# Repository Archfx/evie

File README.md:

# Camaro6 CAD files
### EVIE is my 6<sup>th</sup> gen Camaro

This repository contains various CAD models I have designed for 6th-generation Camaros built on the [alpha platform](https://en.wikipedia.org/wiki/General_Motors_Alpha_platform). 
These models were created using [FreeCAD](https://www.freecad.org/) and [KiCad](https://www.kicad.org/). 

Electric Vacuum Pump
---

The mount is designed for installing the GM electric vacuum pump from the C7 Corvette onto 6th-generation LTG Camaros. It attaches directly to the existing bolt holes in the passenger-side engine compartment, next to the downpipe. No additional drilling is required.

Fire Extinguisher Mount
---

This directly mounts to the rear rails of the passenger seat. 

Assembly Requires the Following Items:
- Fire extinguisher and the mounting bracket (I used a [First Alert](https://www.firstalert.com/))
- Mounting hardware for the bracket
- 2x 6mm steel standoff (24mm height)
- 2x 6mm hex nut and bolt
- Drill

Note: You may need to slightly enlarge the left rail bolt hole to accommodate a 6 mm standoff. Alternatively, a 5 mm standoff can be used without any modification.

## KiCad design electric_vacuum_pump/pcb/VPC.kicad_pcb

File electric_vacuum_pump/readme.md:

Relay Box Parts
----

- CID101-2.8-FS4 Original Yazaki 7116-4153-02 Terminal, YESC 2.8 mm, Female, 3.0 - 4.0 mm² × 2

- MTA 0301504 MiniVAL / Mini Relay Gray Module × 1

- CID101-2.8-MS4 Original Yazaki 7114-4153-02 Terminal , Male, 3.0 - 4.0 mm² × 4

- MTA 1708332-L Mini 280 Female Terminal, Unsealed, 2.5 - 4.0 mm² × 4

- MTA 1708500-L Female Terminal, 630 Series, Unsealed, 0.35 - 0.5 mm² × 8

- MTA 1708502-L Female Terminal, 630 Series, Unsealed, 2.0 - 3.0 mm² × 6

- MTA 0301506 Secondary Lock for 0301504 Gray Module × 1

- CID203-2.3-FS1 Drop In for Sumitomo 1500-0106 Sealed Female 090 Terminals, 0.3 -0.5 mm², Tin Plated × 5

- CID2026J-2.3-21 Drop In for Sumitomo 2-way Sealed Female MT090 Connector 6180-2327, Light Gray × 2

- CID203-2.3-MS2 Drop In for Sumitomo 1500-0105 Male Terminal 090, 0.85 - 1.25 mm², Tin Plating × 5

- CID2026J-2.3-11 Drop In for Sumitomo 2-way Sealed Male MT090 Connector 6187-2317, Light Gray × 2

- MAH-S-112-C-1D2 ISO Mini Relay 60A, 12Vdc, SPDT with Diode Suppression Drop in for Song Chuan 896H-1CH-C-002-12VDC × 1

- MTA 0301590 Cover for a Single Gray Module × 1

- MTA 0301580 Mounting Bracket for Gray Modules × 2

- MTA 0705160 MiniVAL 25 Amp Fuse, White × 3

- CID3110 Original Yazaki 7158-3110-40 Wire Seal, YESC 2.8 mm, Gray, Silicone × 4

- CID101-2.8-MS4 Original Yazaki 7114-4153-02 Terminal , Male, 3.0 - 4.0 mm² × 4

Controller PCB Parts
---

| Id | Designator | Footprint                           | Quantity | Designation     |
|----|------------|-------------------------------------|----------|-----------------|
| 1  | U3         | HPAK_16AH-E_STM                     | 1        | VN5T016AHTR-E   |
| 2  | LED1       | LED_0603_1608Metric                 | 1        | LED_0603        |
| 3  | U2         | Converter_DCDC_TRACO_TSR1-xxxxE_THT | 1        | TSR1-2450E      |
| 4  | R3         | R_0603_1608Metric                   | 1        | 1K_R_0603       |
| 5  | R5         | R_0603_1608Metric                   | 1        | 1k              |
| 6  | J1         | PinHeader_1x01_P2.54mm_Vertical     | 1        | Program         |
| 7  | J2         | PinHeader_1x05_P2.54mm_Vertical     | 1        | Mini Relay Pins |
| 8  | U1         | SOIC-8_3.9x4.9mm_P1.27mm            | 1        | ATtiny412-SS    |
| 9  | C4,C5      | C_0603_1608Metric                   | 2        | 10nf            |
| 10 | R2,R4,R7   | R_0603_1608Metric                   | 3        | 56K             |
| 11 | FB1        | C_0603_1608Metric                   | 1        | BLM18PG121SN1D  |
| 12 | C1         | C_1812_4532Metric                   | 1        | 22uf            |
| 13 | R6         | R_0603_1608Metric                   | 1        | 10R             |
| 14 | C6,C3      | C_0603_1608Metric                   | 2        | 100nf           |
| 15 | R8,R1      | R_0603_1608Metric                   | 2        | 100K            |
| 16 | D1         | D_SMB                               | 1        | SMBJ24A-Q       |
| 17 | D3         | D_SOD-323                           | 1        | PESD5V0S1BA     |
| 18 | C2         | C_1210_3225Metric                   | 1        | 10uf            |

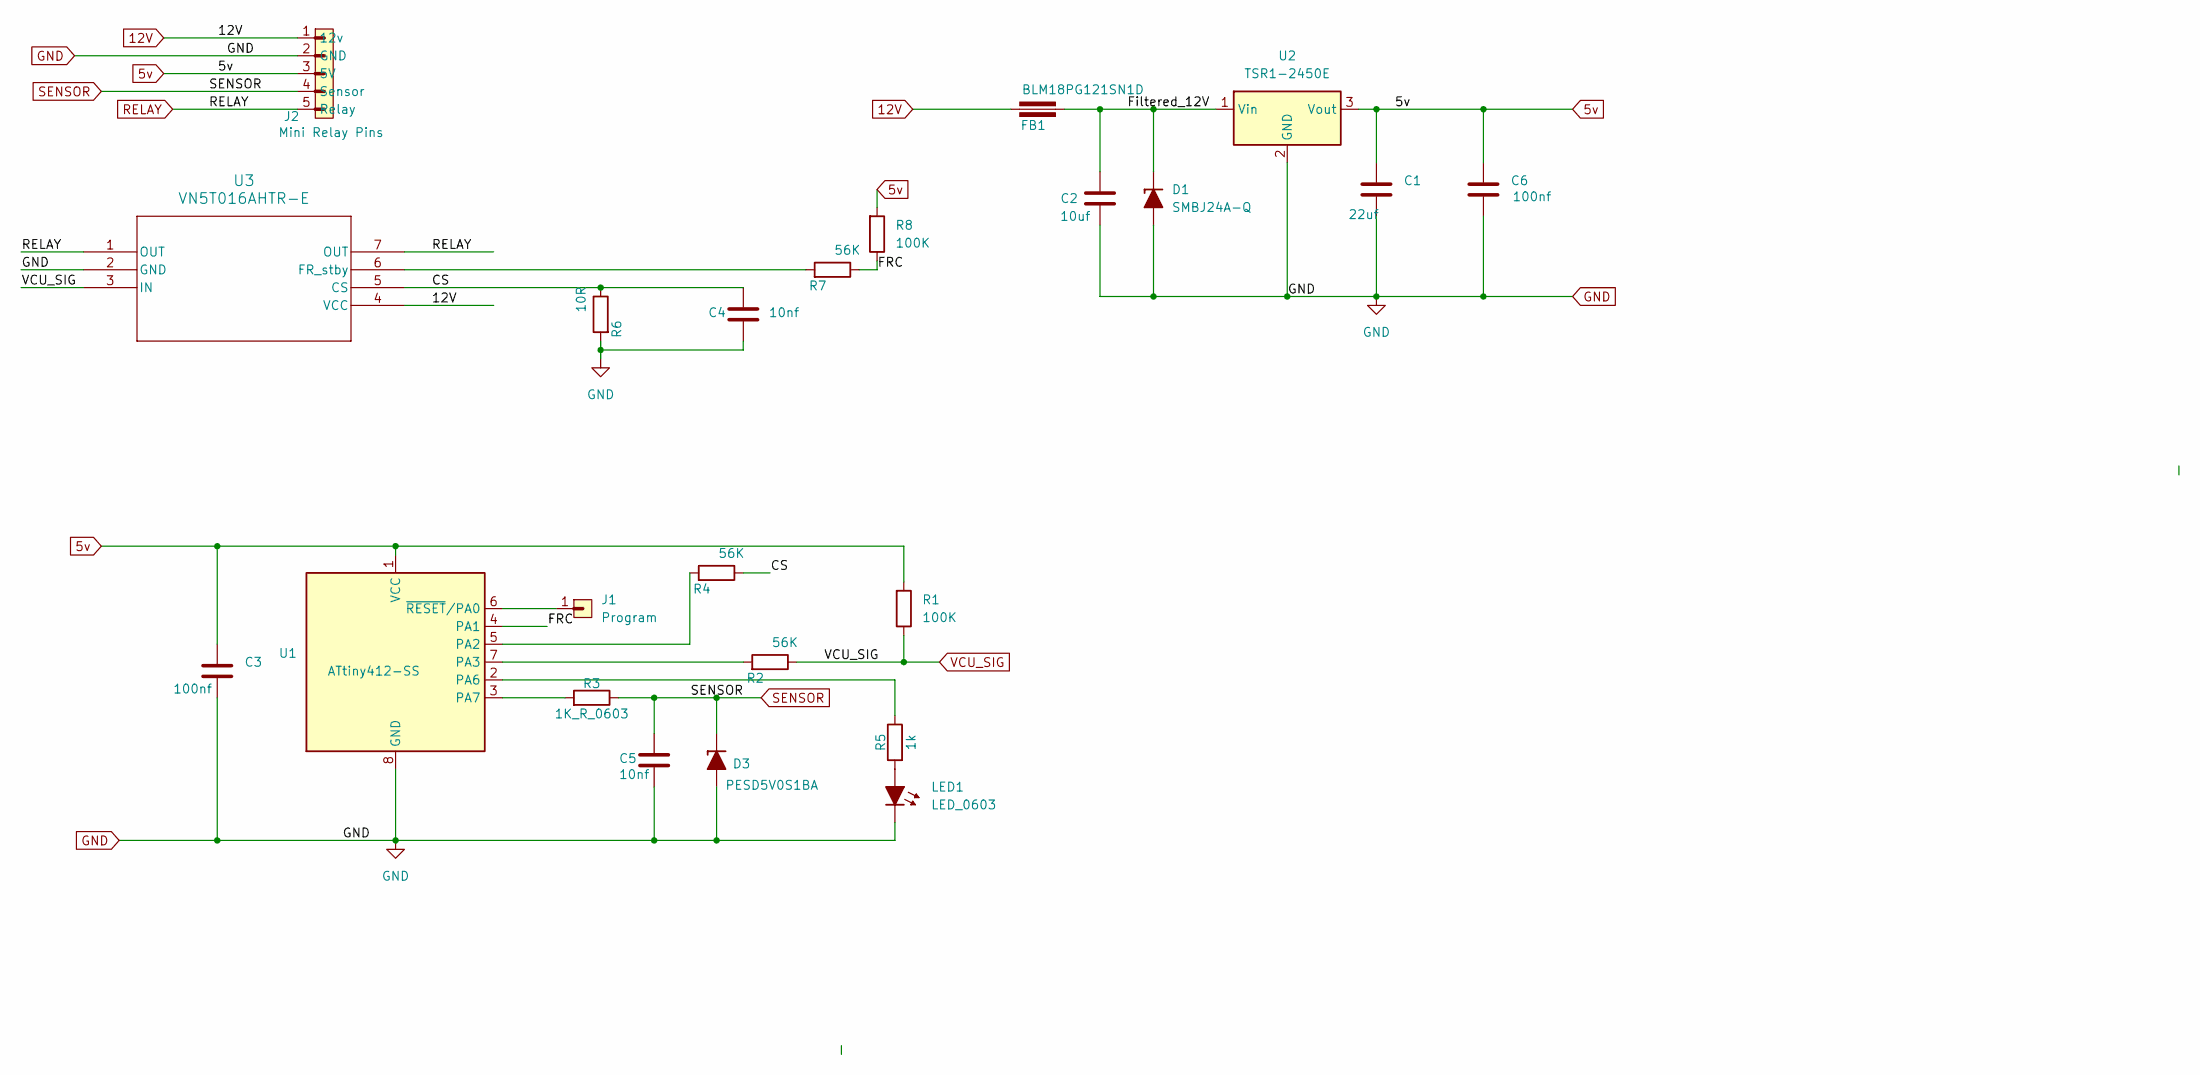
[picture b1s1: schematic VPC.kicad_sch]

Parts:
C1: 22uf; C_1812_4532Metric
C2: 10uf; C_1210_3225Metric
C3, C6: 100nf; C_0603_1608Metric
C4, C5: 10nf; C_0603_1608Metric
D1: SMBJ24A-Q; D_SMB
D3: PESD5V0S1BA; D_SOD-323
FB1: BLM18PG121SN1D; C_0603_1608Metric
J1: Program; PinHeader_1x01_P2.54mm_Vertical
J2: Mini Relay Pins; PinHeader_1x05_P2.54mm_Vertical
LED1: LED_0603; LED_0603_1608Metric
R1, R8: 100K; R_0603_1608Metric
R2, R4, R7: 56K; R_0603_1608Metric
R3: 1K_R_0603; R_0603_1608Metric
R5: 1k; R_0603_1608Metric
R6: 10R; R_0603_1608Metric
U1: ATtiny412-SS; SOIC-8_3.9x4.9mm_P1.27mm
U2: TSR1-2450E; Converter_DCDC_TRACO_TSR1-xxxxE_THT
U3: VN5T016AHTR-E; HPAK_16AH-E_STM

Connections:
5v: C1.1, C3.1, C6.1, J2.3 (5V), R1.1, R8.1, U1.1 (VCC), U2.3 (Vout)
12V: FB1.2, J2.1 (12v), U3.4 (VCC)
/CS: C4.1, R4.2, R6.2, U3.5 (CS)
/FRC: R7.2, R8.2, U1.4 (PA1)
/Filtered_12V: C2.2, D1.1 (K), FB1.1, U2.1 (Vin)
GND: C1.2, C2.1, C3.2, C4.2, C5.2, C6.2, D1.2 (A), D3.2 (A), J2.2 (GND), LED1.1 (K), R6.1, U1.8 (GND), U2.2 (GND), U3.2 (GND)
unnamed: LED1.2 (A), R5.1
unnamed: R4.1, U1.5 (PA2)
unnamed: R2.1, U1.7 (PA3)
unnamed: R5.2, U1.2 (PA6)
unnamed: R3.1, U1.3 (PA7)
unnamed: J1.1, U1.6 (~RESET/PA0)
unnamed: R7.1, U3.6 (FR_stby)
RELAY: J2.5 (Relay), U3.1 (OUT), U3.7 (OUT)
SENSOR: C5.1, D3.1 (K), J2.4 (Sensor), R3.2
VCU_SIG: R1.2, R2.2, U3.3 (IN)

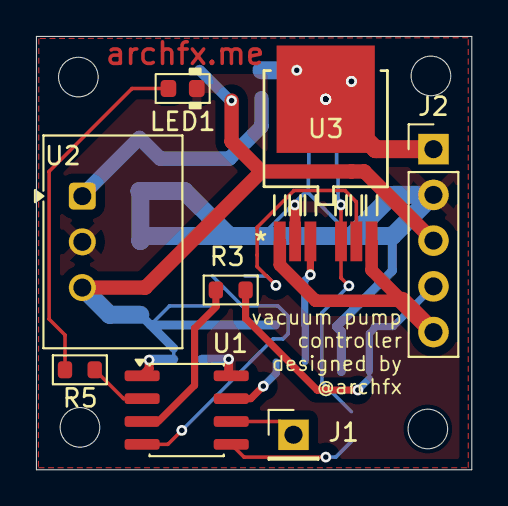
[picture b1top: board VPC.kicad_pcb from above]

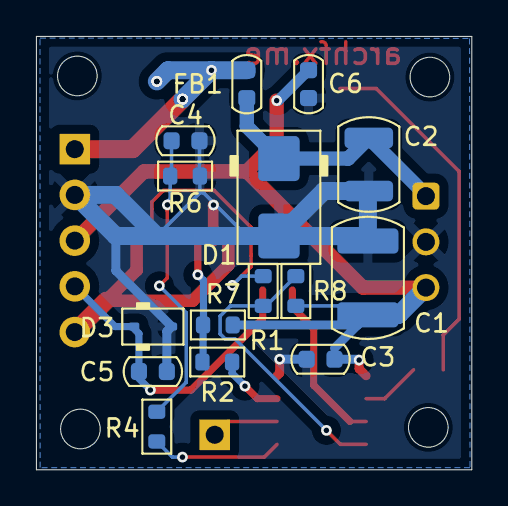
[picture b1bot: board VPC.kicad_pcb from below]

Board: 2 copper layers, 24.2 x 24.1 mm, 23 parts (15 on the bottom side), 16 nets.

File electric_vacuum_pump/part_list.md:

Relay Box Parts
----

- CID101-2.8-FS4 Original Yazaki 7116-4153-02 Terminal, YESC 2.8 mm, Female, 3.0 - 4.0 mm² × 2

- MTA 1708500-L Female Terminal, 630 Series, Unsealed, 0.35 - 0.5 mm² × 6

- MTA 0301504 MiniVAL / Mini Relay Gray Module × 1

- CID101-2.8-MS4 Original Yazaki 7114-4153-02 Terminal , Male, 3.0 - 4.0 mm² × 4

- MTA 1708332-L Mini 280 Female Terminal, Unsealed, 2.5 - 4.0 mm² × 4

- MTA 1708500-L Female Terminal, 630 Series, Unsealed, 0.35 - 0.5 mm² × 8

- MTA 1708502-L Female Terminal, 630 Series, Unsealed, 2.0 - 3.0 mm² × 6

- MTA 0301506 Secondary Lock for 0301504 Gray Module × 1

- CID203-2.3-FS1 Drop In for Sumitomo 1500-0106 Sealed Female 090 Terminals, 0.3 -0.5 mm², Tin Plated × 5

- CID2026J-2.3-21 Drop In for Sumitomo 2-way Sealed Female MT090 Connector 6180-2327, Light Gray × 2

- CID203-2.3-MS2 Drop In for Sumitomo 1500-0105 Male Terminal 090, 0.85 - 1.25 mm², Tin Plating × 5

- CID2026J-2.3-11 Drop In for Sumitomo 2-way Sealed Male MT090 Connector 6187-2317, Light Gray × 2

- MAH-S-112-C-1D2 ISO Mini Relay 60A, 12Vdc, SPDT with Diode Suppression Drop in for Song Chuan 896H-1CH-C-002-12VDC × 1

- MTA 0301590 Cover for a Single Gray Module × 1

- MTA 0301580 Mounting Bracket for Gray Modules × 2

- MTA 0705160 MiniVAL 25 Amp Fuse, White × 3

- CID3110 Original Yazaki 7158-3110-40 Wire Seal, YESC 2.8 mm, Gray, Silicone × 4

- CID101-2.8-MS4 Original Yazaki 7114-4153-02 Terminal , Male, 3.0 - 4.0 mm² × 4


Controller PCB Parts
---

| Id | Designator | Footprint                           | Quantity | Designation     |
|----|------------|-------------------------------------|----------|-----------------|
| 1  | U3         | HPAK_16AH-E_STM                     | 1        | VN5T016AHTR-E   |
| 2  | LED1       | LED_0603_1608Metric                 | 1        | LED_0603        |
| 3  | U2         | Converter_DCDC_TRACO_TSR1-xxxxE_THT | 1        | TSR1-2450E      |
| 4  | R3         | R_0603_1608Metric                   | 1        | 1K_R_0603       |
| 5  | R5         | R_0603_1608Metric                   | 1        | 1k              |
| 6  | J1         | PinHeader_1x01_P2.54mm_Vertical     | 1        | Program         |
| 7  | J2         | PinHeader_1x05_P2.54mm_Vertical     | 1        | Mini Relay Pins |
| 8  | U1         | SOIC-8_3.9x4.9mm_P1.27mm            | 1        | ATtiny412-SS    |
| 9  | C4,C5      | C_0603_1608Metric                   | 2        | 10nf            |
| 10 | R2,R4,R7   | R_0603_1608Metric                   | 3        | 56K             |
| 11 | FB1        | C_0603_1608Metric                   | 1        | BLM18PG121SN1D  |
| 12 | C1         | C_1812_4532Metric                   | 1        | 22uf            |
| 13 | R6         | R_0603_1608Metric                   | 1        | 10R             |
| 14 | C6,C3      | C_0603_1608Metric                   | 2        | 100nf           |
| 15 | R8,R1      | R_0603_1608Metric                   | 2        | 100K            |
| 16 | D1         | D_SMB                               | 1        | SMBJ24A-Q       |
| 17 | D3         | D_SOD-323                           | 1        | PESD5V0S1BA     |
| 18 | C2         | C_1210_3225Metric                   | 1        | 10uf            |

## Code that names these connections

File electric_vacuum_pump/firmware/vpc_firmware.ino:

// ATtiny412 (megaTinyCore)
// PA7 = analog input (vacuum sensor)
// PA6 = LED indicator
// PA3 = relay control (HIGH = pump ON)

const uint8_t LED_PIN    = PIN_PA6;
const uint8_t RELAY_PIN  = PIN_PA3;
const uint8_t SENSOR_PIN = PIN_PA7;

// Hysteresis thresholds
const int START_ADC = (int)(3.1f / 5.0f * 1023.0f + 0.5f);
const int STOP_ADC  = (int)(3.5f / 5.0f * 1023.0f + 0.5f);

// Timing protections
const uint32_t MIN_ON_TIME_MS  = 3000;
const uint32_t MIN_OFF_TIME_MS = 1000;

// Sensor fault limits
const int SENSOR_MIN = 10;
const int SENSOR_MAX = 1013;

enum PumpState {
  PUMP_OFF,
  PUMP_ON,
  FAULT
};

PumpState state = PUMP_OFF;

uint32_t stateChangeTime = 0;

int readFilteredSensor() {

  const int samples = 8;
  long sum = 0;

  for (int i = 0; i < samples; i++) {
    sum += analogRead(SENSOR_PIN);
  }

  return sum / samples;
}

void setPump(bool on) {

  digitalWrite(RELAY_PIN, on ? HIGH : LOW);
  digitalWrite(LED_PIN, on ? HIGH : LOW);

  stateChangeTime = millis();
}

void startupBlink() {

  digitalWrite(LED_PIN, HIGH);
  delay(80);
  digitalWrite(LED_PIN, LOW);
  delay(80);

  digitalWrite(LED_PIN, HIGH);
  delay(180);
  digitalWrite(LED_PIN, LOW);
}

void setup() {

  pinMode(LED_PIN, OUTPUT);
  pinMode(RELAY_PIN, OUTPUT);

  startupBlink();

  setPump(false);

  delay(2000); // allow sensor to stabilize
}

void loop() {

  int sensor = readFilteredSensor();
  uint32_t now = millis();

  // Detect sensor fault
  if (sensor < SENSOR_MIN || sensor > SENSOR_MAX) {
    state = FAULT;
  }

  switch (state) {

    case PUMP_OFF:

      if (sensor < START_ADC) {

        setPump(true);
        state = PUMP_ON;
      }

      break;

    case PUMP_ON:

      // If vacuum drops again, reset timer
      if (sensor < START_ADC) {
        stateChangeTime = now;
      }

      // Only stop if condition is continuously satisfied
      if (sensor > STOP_ADC &&
          (now - stateChangeTime) > MIN_ON_TIME_MS) {

        setPump(false);
        state = PUMP_OFF;
      }

      break;

    case FAULT:

      // Fail-safe: run pump continuously
      setPump(true);

      break;
  }

  delay(10);
}

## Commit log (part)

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2026-01-26 cad files added
2026-01-27 sync
